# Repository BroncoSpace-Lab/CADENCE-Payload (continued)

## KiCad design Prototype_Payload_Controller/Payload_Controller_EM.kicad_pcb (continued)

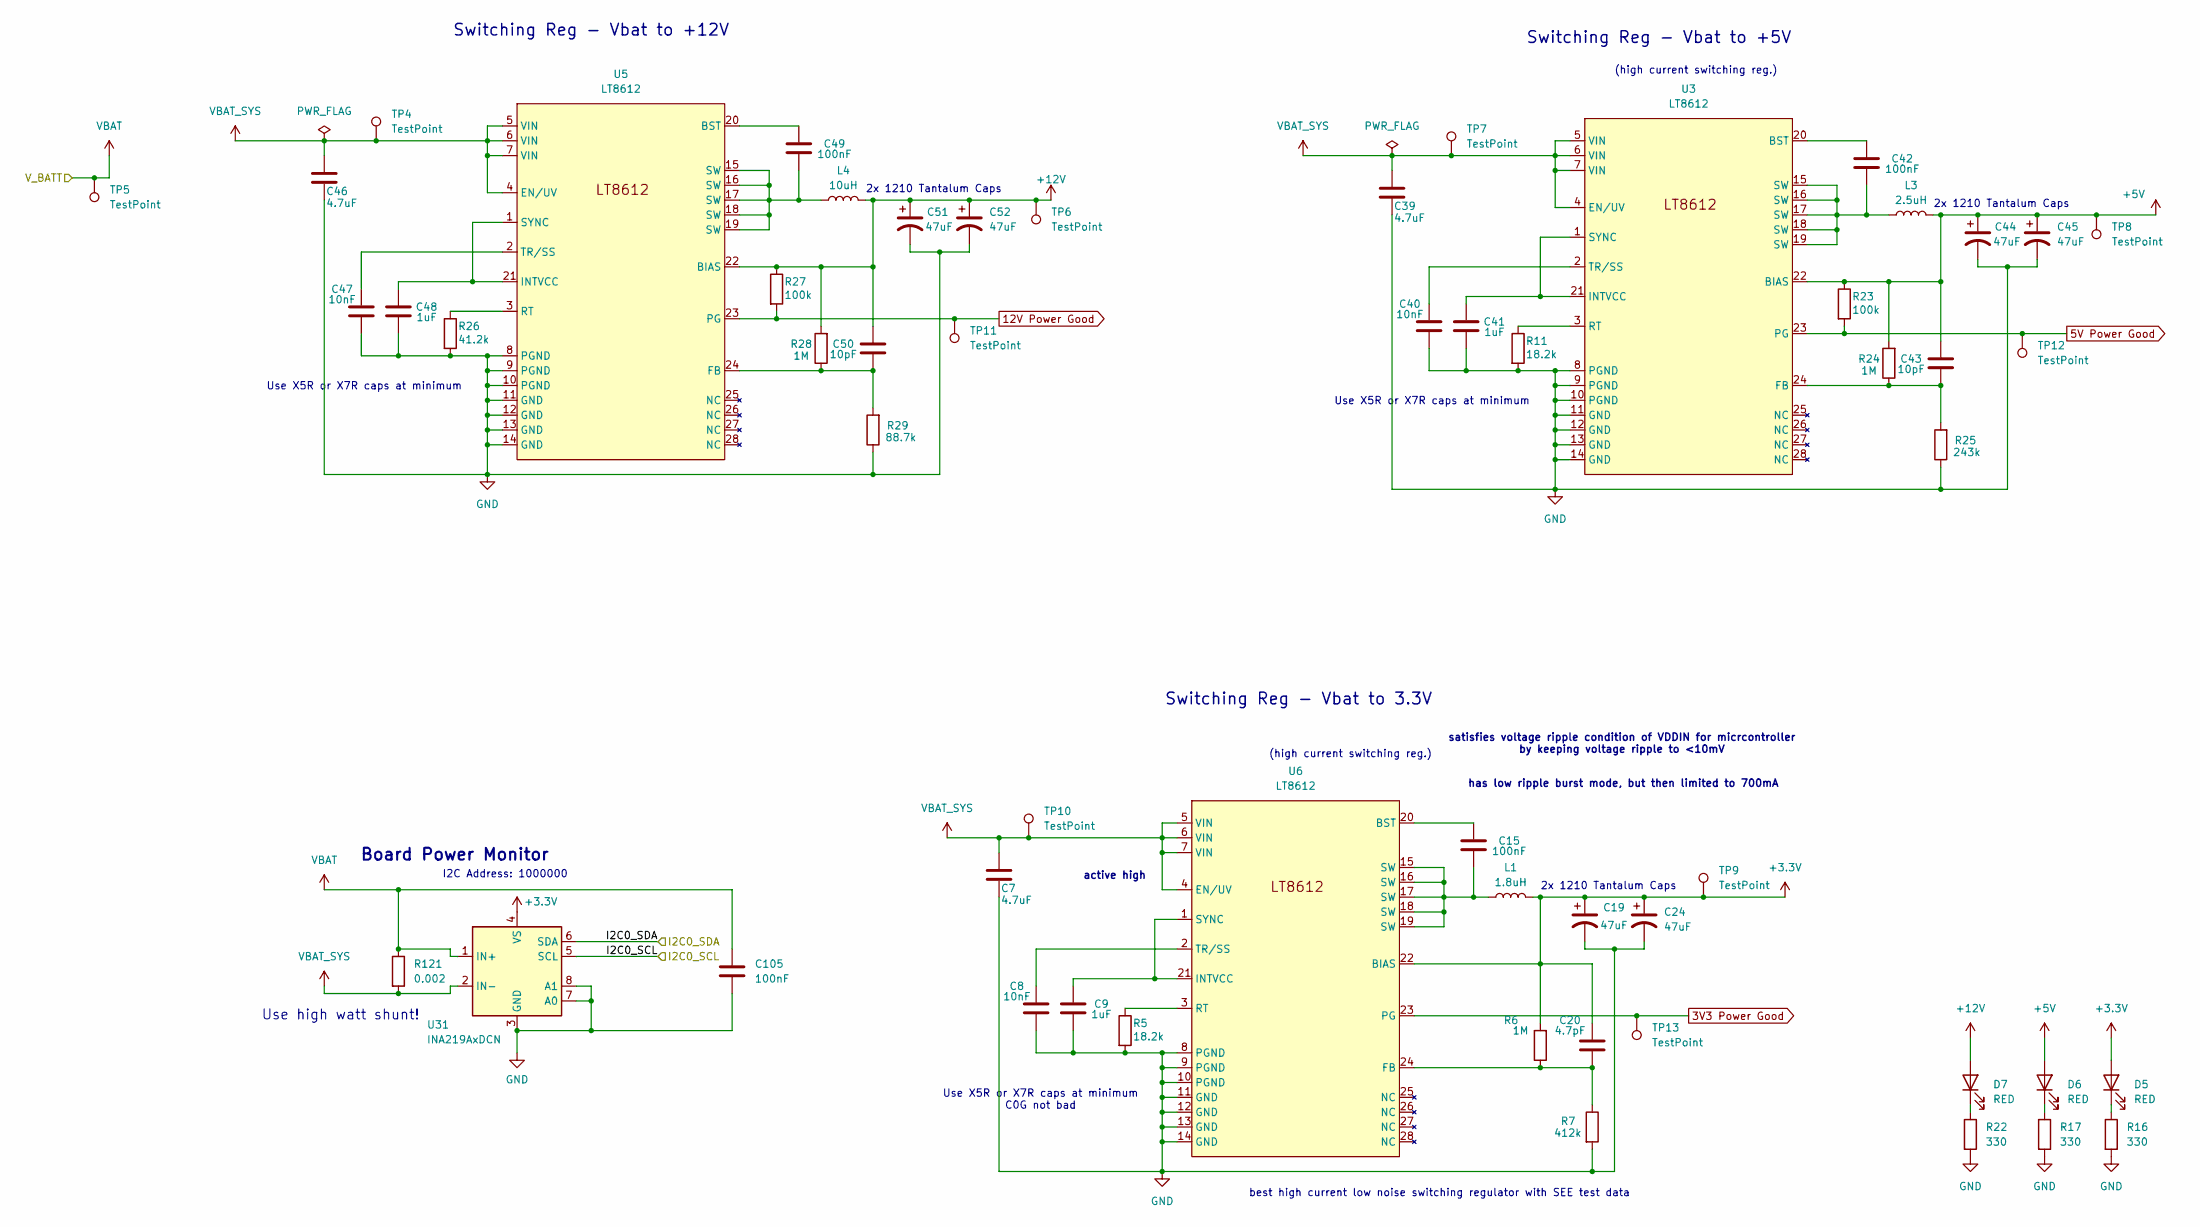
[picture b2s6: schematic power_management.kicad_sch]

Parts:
C7, C39, C46: 4.7uF; C_0603_1608Metric
C8: 10nF; C_0603_1608Metric
C9, C41, C48: 1uF; C_0603_1608Metric
C15, C105: 100nF; C_0603_1608Metric
C19, C24: 47uF; C_0603_1608Metric
C20: 4.7pF; C_0603_1608Metric
C40, C47: 10nF; C_0402_1005Metric
C42, C49: 100nF; C_0402_1005Metric
C43, C50: 10pF; C_0402_1005Metric
C44, C45, C51, C52: 47uF; C_1206_3216Metric
D5, D6, D7: RED; LED_0603_1608Metric
L1: 1.8uH; L_6.3x6.3_H3
L3: 2.5uH; L_6.3x6.3_H3
L4: 10uH; L_6.3x6.3_H3
R5, R11: 18.2k; R_0402_1005Metric
R6: 1M; R_0402_1005Metric
R7: 412k; R_0402_1005Metric
R16, R17, R22: 330; R_0402_1005Metric
R23, R27: 100k; R_0402_1005Metric
R24, R28: 1M; R_0603_1608Metric
R25: 243k; R_0402_1005Metric
R26: 41.2k; R_0402_1005Metric
R29: 88.7k; R_0402_1005Metric
R121: 0.002; R_0402_1005Metric
TP4, TP5, TP6, TP7, TP8, TP9, TP10, TP11, TP12, TP13: TestPoint; TestPoint_Pad_1.0x1.0mm
U3, U5, U6: LT8612; QFN-28_UDE_LTI
U31: INA219AxDCN; SOT-23-8

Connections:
3V3 Power Good: TP13.1, U6.23 (PG)
5V Power Good: R23.2, TP12.1, U3.23 (PG)
12V Power Good: R27.2, TP11.1, U5.23 (PG)
+3.3V: C19.1, C20.2, C24.1, D5.2 (A), L1.2, R6.2, TP9.1, U6.22 (BIAS), U31.4 (VS); also elsewhere on the board
+5V: C43.2, C44.1, C45.1, D6.2 (A), L3.2, R23.1, R24.2, TP8.1, U3.22 (BIAS); also elsewhere on the board
+12V: C50.2, C51.1, C52.1, D7.2 (A), L4.2, R27.1, R28.2, TP6.1, U5.22 (BIAS); also elsewhere on the board
/Peripherals/I2C0_SCL: U31.5 (SCL); also elsewhere on the board
/Peripherals/I2C0_SDA: U31.6 (SDA); also elsewhere on the board
GND: C7.2, C8.1, C9.1, C19.2, C24.2, C39.2, C40.1, C41.1, C44.2, C45.2, C46.2, C47.1, C48.1, C51.2, C52.2, C105.2, R5.2, R7.2, R11.2, R16.2, R17.2, R22.2, R25.1, R26.2, R29.1, U3.8 (PGND), U3.9 (PGND), U3.10 (PGND), U3.11 (GND), U3.12 (GND), U3.13 (GND), U3.14 (GND), U5.8 (PGND), U5.9 (PGND), U5.10 (PGND), U5.11 (GND), U5.12 (GND), U5.13 (GND), U5.14 (GND), U6.8 (PGND), U6.9 (PGND), U6.10 (PGND), U6.11 (GND), U6.12 (GND), U6.13 (GND), U6.14 (GND), U31.3 (GND), U31.7 (A0), U31.8 (A1); also elsewhere on the board
unnamed: C15.1, L1.1, U6.15 (SW), U6.16 (SW), U6.17 (SW), U6.18 (SW), U6.19 (SW)
unnamed: C42.1, L3.1, U3.15 (SW), U3.16 (SW), U3.17 (SW), U3.18 (SW), U3.19 (SW)
unnamed: C49.1, L4.1, U5.15 (SW), U5.16 (SW), U5.17 (SW), U5.18 (SW), U5.19 (SW)
unnamed: D5.1 (K), R16.1
unnamed: D6.1 (K), R17.1
unnamed: D7.1 (K), R22.1
unnamed: C42.2, U3.20 (BST)
unnamed: C43.1, R24.1, R25.2, U3.24 (FB)
unnamed: C41.2, U3.1 (SYNC), U3.21 (INTVCC)
unnamed: R11.1, U3.3 (RT)
unnamed: C40.2, U3.2 (TR/SS)
unnamed: C49.2, U5.20 (BST)
unnamed: C50.1, R28.1, R29.2, U5.24 (FB)
unnamed: C48.2, U5.1 (SYNC), U5.21 (INTVCC)
unnamed: R26.1, U5.3 (RT)
unnamed: C47.2, U5.2 (TR/SS)
unnamed: C15.2, U6.20 (BST)
unnamed: C20.1, R6.1, R7.1, U6.24 (FB)
unnamed: C9.2, U6.1 (SYNC), U6.21 (INTVCC)
unnamed: R5.1, U6.3 (RT)
unnamed: C8.2, U6.2 (TR/SS)
VBAT: C105.1, R121.1, TP5.1, U31.1 (IN+); also elsewhere on the board
VBAT_SYS: C7.1, C39.1, C46.1, R121.2, TP4.1, TP7.1, TP10.1, U3.4 (EN/UV), U3.5 (VIN), U3.6 (VIN), U3.7 (VIN), U5.4 (EN/UV), U5.5 (VIN), U5.6 (VIN), U5.7 (VIN), U6.4 (EN/UV), U6.5 (VIN), U6.6 (VIN), U6.7 (VIN), U31.2 (IN-)

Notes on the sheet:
2x 1210 Tantalum Caps
Board Power Monitor
best high current low noise switching regulator with SEE test data
satisfies voltage ripple condition of VDDIN for micrcontroller by keeping voltage ripple to <10mV
Switching Reg - Vbat to +5V
Use X5R or X7R caps at minimum
Use high watt shunt!
Switching Reg - Vbat to +12V
I2C Address: 1000000
Use X5R or X7R caps at minimum C0G not bad
(high current switching reg.)
has low ripple burst mode, but then limited to 700mA
active high
Switching Reg - Vbat to 3.3V

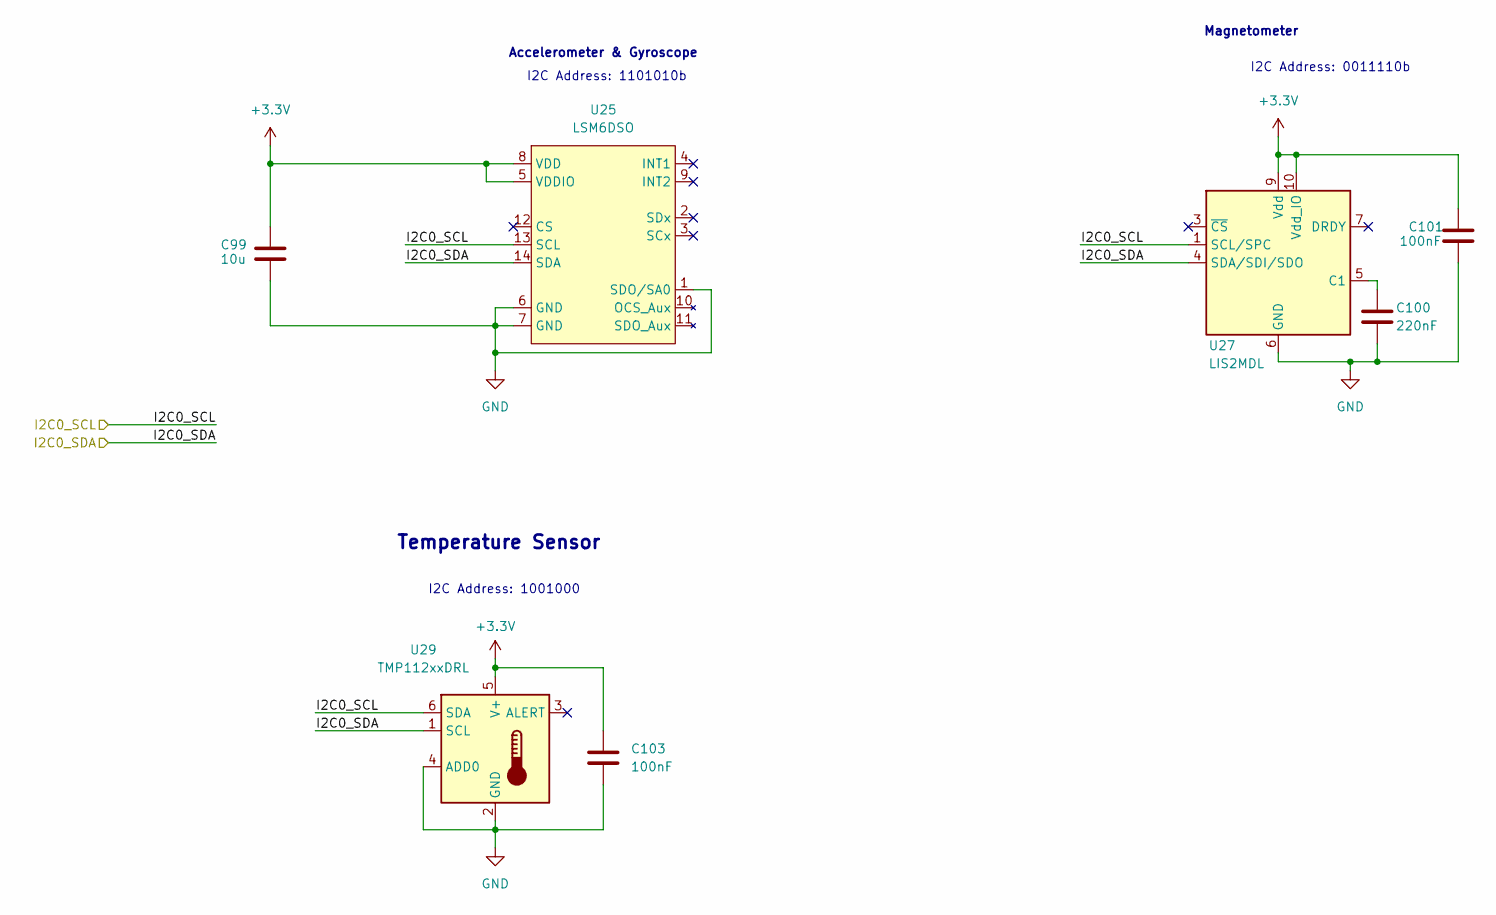
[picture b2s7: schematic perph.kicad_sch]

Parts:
C99: 10u; C_0603_1608Metric
C100: 220nF; C_0603_1608Metric
C101, C103: 100nF; C_0603_1608Metric
U25: LSM6DSO; LGA-14_L3.0-W2.5-P0.50-TL
U27: LIS2MDL; LGA-12_2x2mm_P0.5mm
U29: TMP112xxDRL; SOT-563

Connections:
+3.3V: C99.1, C101.1, C103.1, U25.5 (VDDIO), U25.8 (VDD), U27.9 (Vdd), U27.10 (Vdd_IO), U29.5 (V+); also elsewhere on the board
/Peripherals/I2C0_SCL: U25.13 (SCL), U27.1 (SCL/SPC), U29.6 (SDA); also elsewhere on the board
/Peripherals/I2C0_SDA: U25.14 (SDA), U27.4 (SDA/SDI/SDO), U29.1 (SCL); also elsewhere on the board
GND: C99.2, C100.2, C101.2, C103.2, U25.1 (SDO/SA0), U25.6 (GND), U25.7 (GND), U27.6 (GND), U27.8 (GND), U29.2 (GND), U29.4 (ADD0); also elsewhere on the board
unnamed: C100.1, U27.5 (C1)

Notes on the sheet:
Temperature Sensor
I2C Address: 0011110b
Accelerometer & Gyroscope
Magnetometer
I2C Address: 1001000
I2C Address: 1101010b

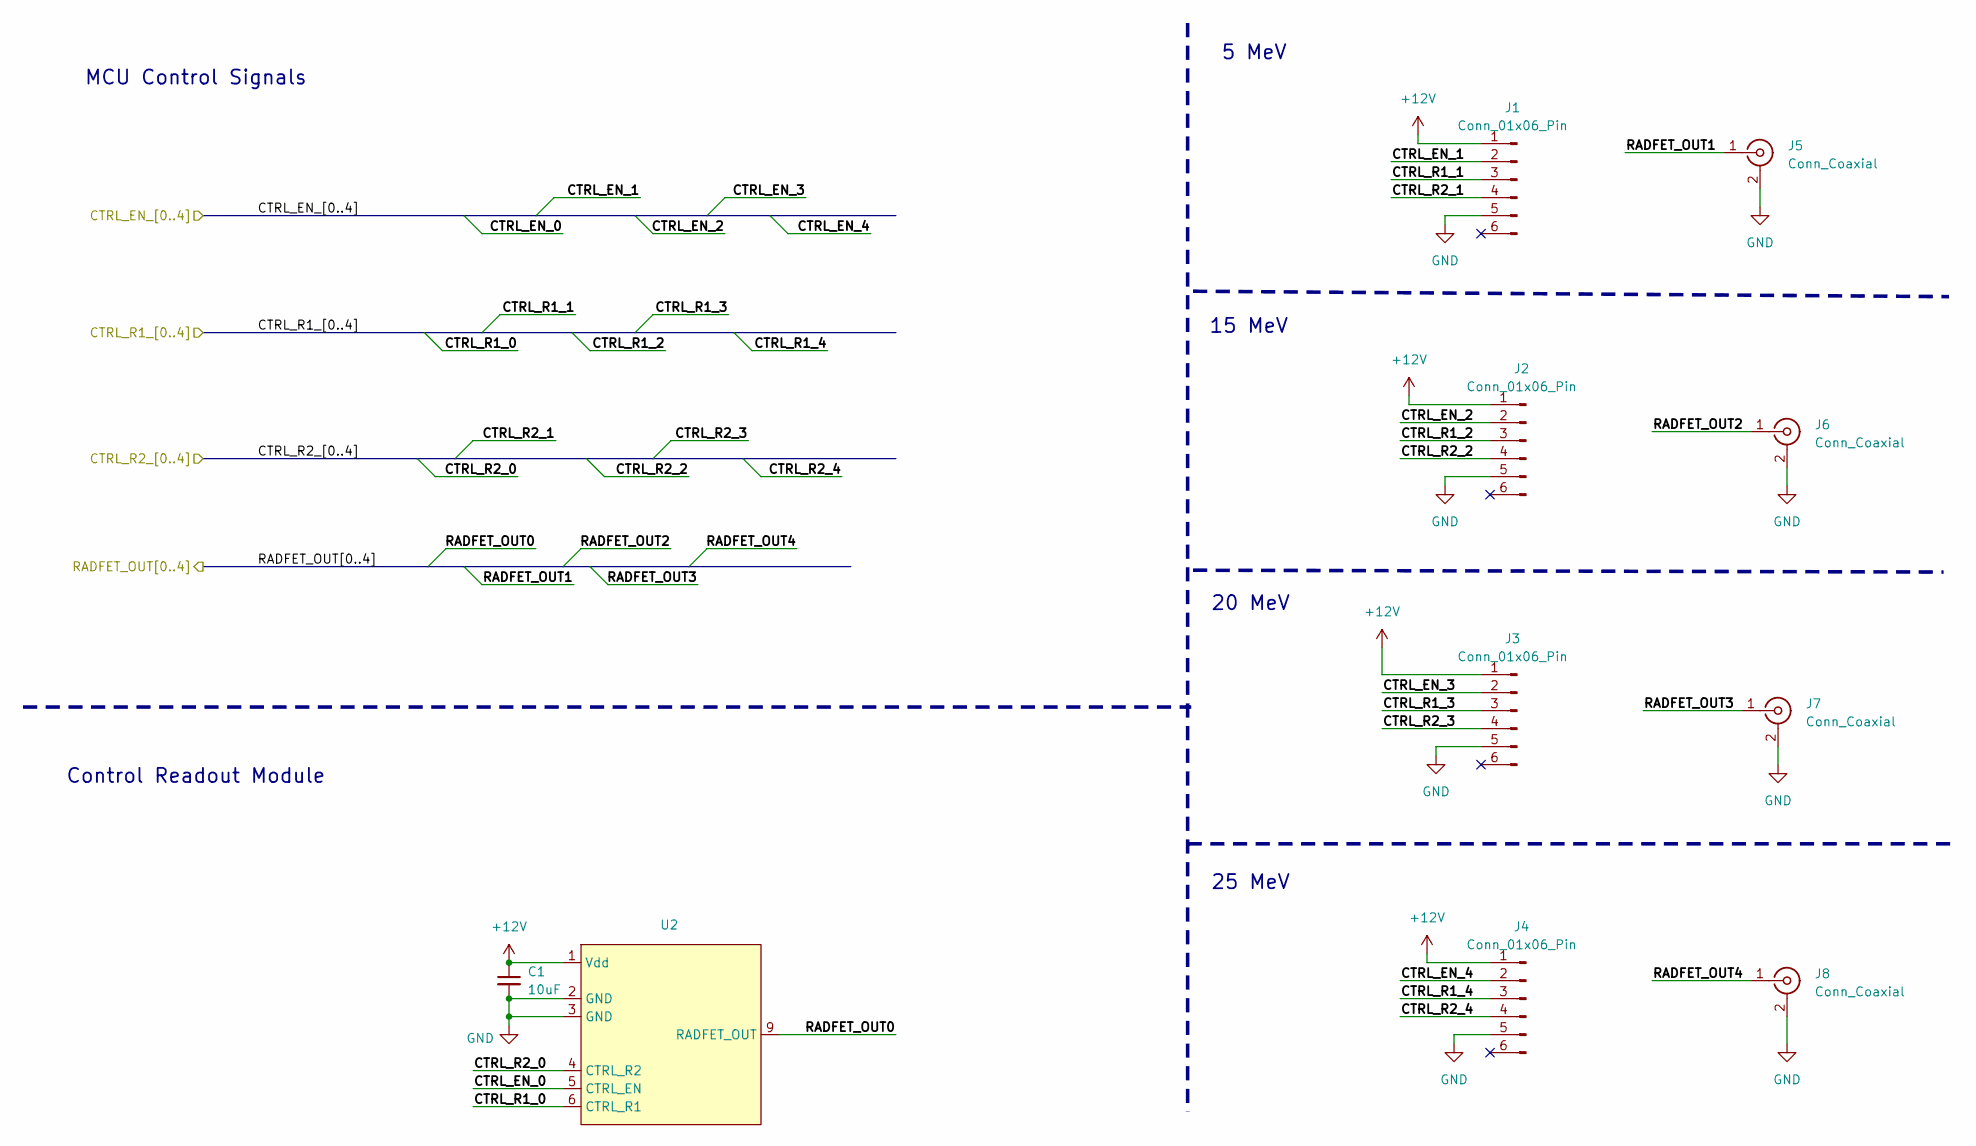
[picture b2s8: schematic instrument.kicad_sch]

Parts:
C1: 10uF; C_0603_1608Metric
J1, J2, J3, J4: Conn_01x06_Pin; Hirose_DF11-6DP-2DSA_2x03_P2.00mm_Vertical
J5, J6, J7, J8: Conn_Coaxial; MMCX_Molex_73415-1471_Vertical
U2: RM-VT01-A

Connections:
+12V: C1.1, J1.1, J2.1, J3.1, J4.1, U2.1 (Vdd); also elsewhere on the board
/Instrument/CTRL_EN_0: U2.5 (CTRL_EN); also elsewhere on the board
/Instrument/CTRL_EN_1: J1.2; also elsewhere on the board
/Instrument/CTRL_EN_2: J2.2; also elsewhere on the board
/Instrument/CTRL_EN_3: J3.2; also elsewhere on the board
/Instrument/CTRL_EN_4: J4.2; also elsewhere on the board
/Instrument/CTRL_R1_0: U2.6 (CTRL_R1); also elsewhere on the board
/Instrument/CTRL_R1_1: J1.3; also elsewhere on the board
/Instrument/CTRL_R1_2: J2.3; also elsewhere on the board
/Instrument/CTRL_R1_3: J3.3; also elsewhere on the board
/Instrument/CTRL_R1_4: J4.3; also elsewhere on the board
/Instrument/CTRL_R2_0: U2.4 (CTRL_R2); also elsewhere on the board
/Instrument/CTRL_R2_1: J1.4; also elsewhere on the board
/Instrument/CTRL_R2_2: J2.4; also elsewhere on the board
/Instrument/CTRL_R2_3: J3.4; also elsewhere on the board
/Instrument/CTRL_R2_4: J4.4; also elsewhere on the board
/Instrument/RADFET_OUT0: U2.9 (RADFET_OUT); also elsewhere on the board
/Instrument/RADFET_OUT1: J5.1 (In); also elsewhere on the board
/Instrument/RADFET_OUT2: J6.1 (In); also elsewhere on the board
/Instrument/RADFET_OUT3: J7.1 (In); also elsewhere on the board
/Instrument/RADFET_OUT4: J8.1 (In); also elsewhere on the board
GND: C1.2, J1.5, J2.5, J3.5, J4.5, J5.2 (Ext), J6.2 (Ext), J7.2 (Ext), J8.2 (Ext), U2.2 (GND), U2.3 (GND); also elsewhere on the board

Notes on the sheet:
15 MeV
Control Readout Module
5 MeV
MCU Control Signals
20 MeV
25 MeV

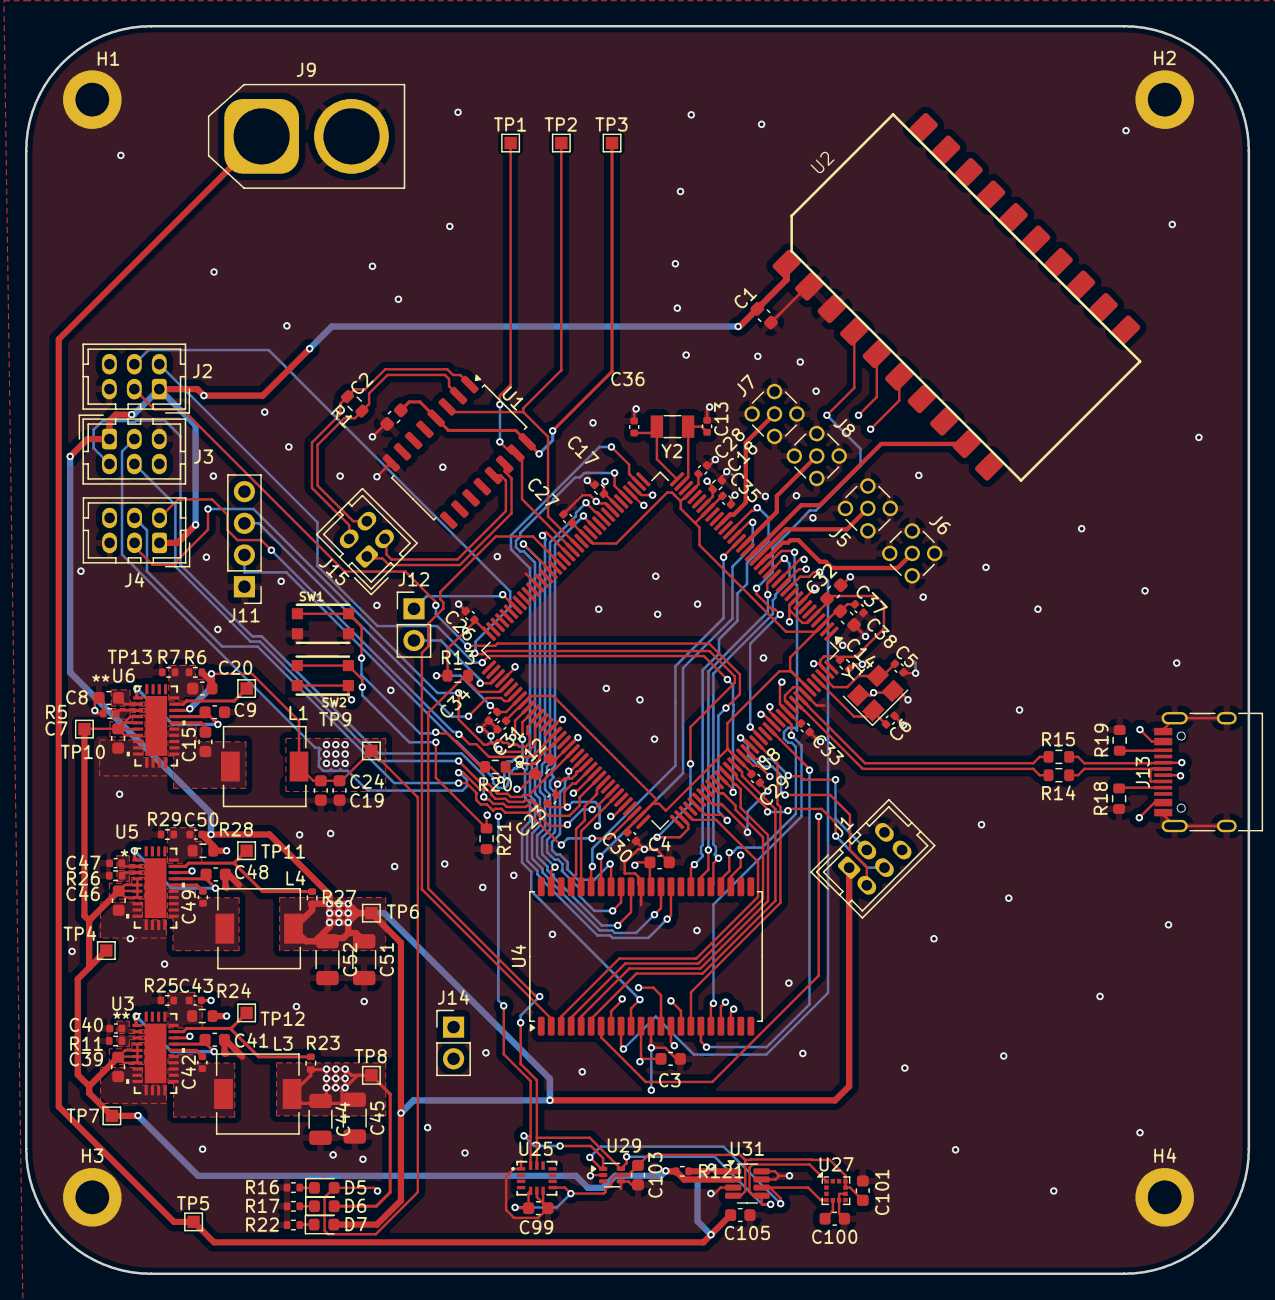
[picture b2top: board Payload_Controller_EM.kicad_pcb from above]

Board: 4 copper layers, 98.0 x 100.0 mm, 126 parts (0 on the bottom side), 110 nets.

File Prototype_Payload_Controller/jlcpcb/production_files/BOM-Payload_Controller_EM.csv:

Comment,Designator,Footprint,LCSC,Quantity
0.002,R121,R_0402_1005Metric,C92124,1
1.8uH,L1,L_6.3x6.3_H3,C19191693,1
100k,"R23,R27",R_0402_1005Metric,C25530,2
100nF,"C14,C17,C18,C23,C26,C27,C28,C29,C30,C31,C33,C34,C35,C37,C42,C49",R_0402_1005Metric,C1525,16
100nF,"C101,C103,C105,C15",C_0603_1608Metric,C1590,4
10k,"R20,R21",R_0603_1608Metric,C12030,2
10nF,"C40,C47",C_0402_1005Metric,C1524,2
10nF,C8,C_0603_1608Metric,C1589,1
10pF,"C43,C50",C_0402_1005Metric,C1545,2
10u,C99,C_0603_1608Metric,C19702,1
10uF,"C1,C2,C3,C4",C_0603_1608Metric,C5530690,4
10uH,L4,L_6.3x6.3_H3,C16218,1
120,R1,R_0603_1608Metric,C12391,1
12pF,"C5,C6",C_0402_1005Metric,C1547,2
17pF,"C13,C36",C_0402_1005Metric,C1517782,2
18.2k,"R11,R5",R_0402_1005Metric,C11724,2
1M,R6,R_0402_1005Metric,C11868,1
1M,"R24,R28",R_0603_1608Metric,C12038,2
1uF,"C38,C41,C48,C9",C_0603_1608Metric,C1592,4
2.5uH,L3,L_6.3x6.3_H3,C222963,1
22,"R14,R15",R_0603_1608Metric,C1010,2
220nF,C100,C_0603_1608Metric,C1606,1
243k,R25,R_0402_1005Metric,C43249,1
330,"R16,R17,R22",R_0402_1005Metric,C12246,3
4.7k,"R12,R13",R_0603_1608Metric,C1980,2
4.7pF,C20,C_0603_1608Metric,C1669,1
4.7uF,"C32,C39,C46,C7",C_0603_1608Metric,C19666,4
41.2k,R26,R_0402_1005Metric,C26978,1
412k,R7,R_0402_1005Metric,C27008,1
47uF,"C19,C24",C_0603_1608Metric,C140782,2
5.1k,"R18,R19",R_0603_1608Metric,C12028,2
88.7k,R29,R_0402_1005Metric,C25922,1
ABM3B-12.000MHZ-B2-T,Y1,Crystal_SMD_3225-4Pin_3.2x2.5mm,C596868,1
ABS07-32.768KHZ-T,Y2,Crystal_SMD_3215-2Pin_3.2x1.5mm,C130253,1
Conn_01x02,"J12,J14",PinHeader_1x02_P2.54mm_Vertical,C42431798,2
Conn_01x04,J11,PinHeader_1x04_P2.54mm_Vertical,C53055674,1
Conn_01x06_Pin,"J1,J2,J3,J4",Hirose_DF11-6DP-2DSA_2x03_P2.00mm_Vertical,C506668,4
Conn_02x02_Top_Bottom,J15,Hirose_DF11-4DP-2DSA_2x02_P2.00mm_Vertical,C506665,1
Conn_Coaxial,"J5,J6,J7,J8",MMCX_Molex_73415-1471_Vertical,C588477,4
INA219AxDCN,U31,SOT-23-8,C87469,1
KMR2,"SW1,SW2",BTN_KMR2_4.6X2.8,C72443,2
LIS2MDL,U27,LGA-12_2x2mm_P0.5mm,C919695,1
LSM6DSO,U25,LGA-14_L3.0-W2.5-P0.50-TL,C481766,1
LT8612,"U3,U5,U6",QFN-28_UDE_LTI,C580313,3
RED,"D5,D6,D7",LED_0603_1608Metric,C1034,3
SN65C1168ERGYR,U1,SOP-16_4.55x10.3mm_P1.27mm,C529555,1
TMP112xxDRL,U29,SOT-563,C28927,1
USB_C_Receptacle_USB2.0_16P,J13,USB_C_Receptacle_HRO_TYPE-C-31-M-12,C165948,1
~,U4,TSOP-II-44_10.16x18.41mm_P0.8mm,,1
47uF,C52,C_1206_3216Metric,,1
47uF,C45,C_1206_3216Metric,,1
47uF,C51,C_1206_3216Metric,,1
47uF,C44,C_1206_3216Metric,,1

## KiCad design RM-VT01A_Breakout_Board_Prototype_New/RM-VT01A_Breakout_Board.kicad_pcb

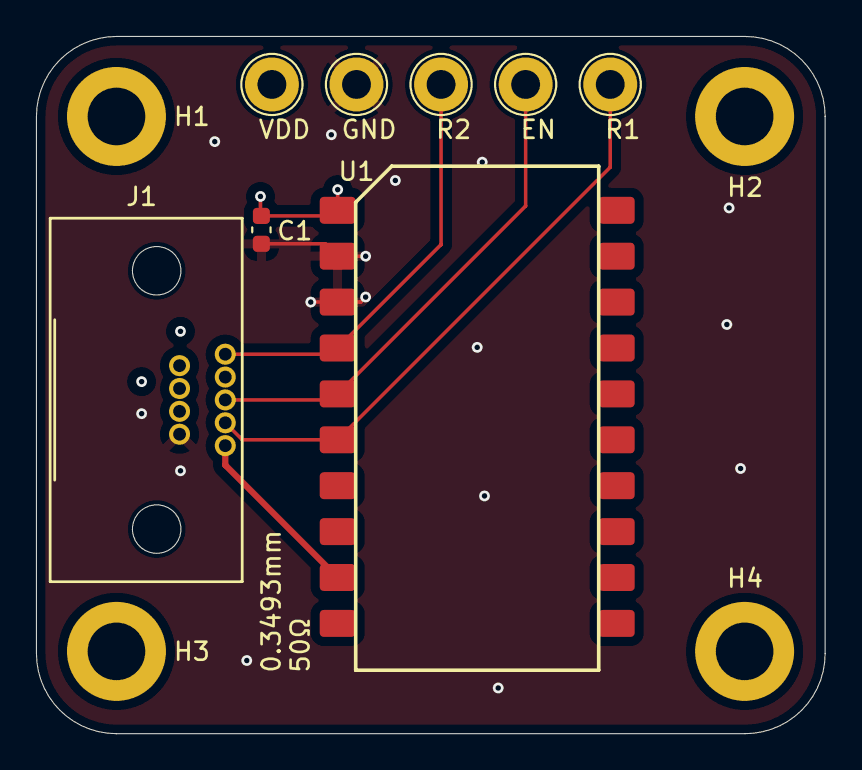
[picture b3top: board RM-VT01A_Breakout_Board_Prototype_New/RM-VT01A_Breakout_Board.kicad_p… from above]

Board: 4 copper layers, 43.8 x 38.7 mm, 12 parts (0 on the bottom side), 6 nets.

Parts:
C1: 10uF; C_0603_1608Metric
EN: TestPoint; TestPoint_Loop_D2.60mm_Drill1.6mm_Beaded
GND: TestPoint; TestPoint_Loop_D2.60mm_Drill1.6mm_Beaded
H1, H2, H3, H4: MountingHole; MountingHole_3.2mm_M3_ISO14580_Pad
J1: DE9_Pins; CONN_381-009_NRC
R1, R2: TestPoint; TestPoint_Loop_D2.60mm_Drill1.6mm_Beaded
U1: RM-VT01-A
VDD: TestPoint; TestPoint_Loop_D2.60mm_Drill1.6mm_Beaded

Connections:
CONN_COAXIAL: J1.5, U1.9 (RADFET_OUT)
CTRL_EN: EN.1, J1.3, U1.5 (CTRL_EN)
CTRL_R1: J1.4, R1.1, U1.6 (CTRL_R1)
CTRL_R2: J1.1, R2.1, U1.4 (CTRL_R2)
GND: C1.2, GND.1, J1.9, U1.2 (GND), U1.3 (GND)
VDD: C1.1, J1.6, U1.1 (Vdd), VDD.1
